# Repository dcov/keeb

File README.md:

# keeb

### controller
Contains the KiCad project files for the main micro controller.
Since this is a split keyboard, this controller is designed to be used in master and slave mode.

### sensor
Contains the KiCad project files for the mouse sensor board for the trackballs.

### stick
Contains the KiCad project files for the joystick boards.

### other components are WIP

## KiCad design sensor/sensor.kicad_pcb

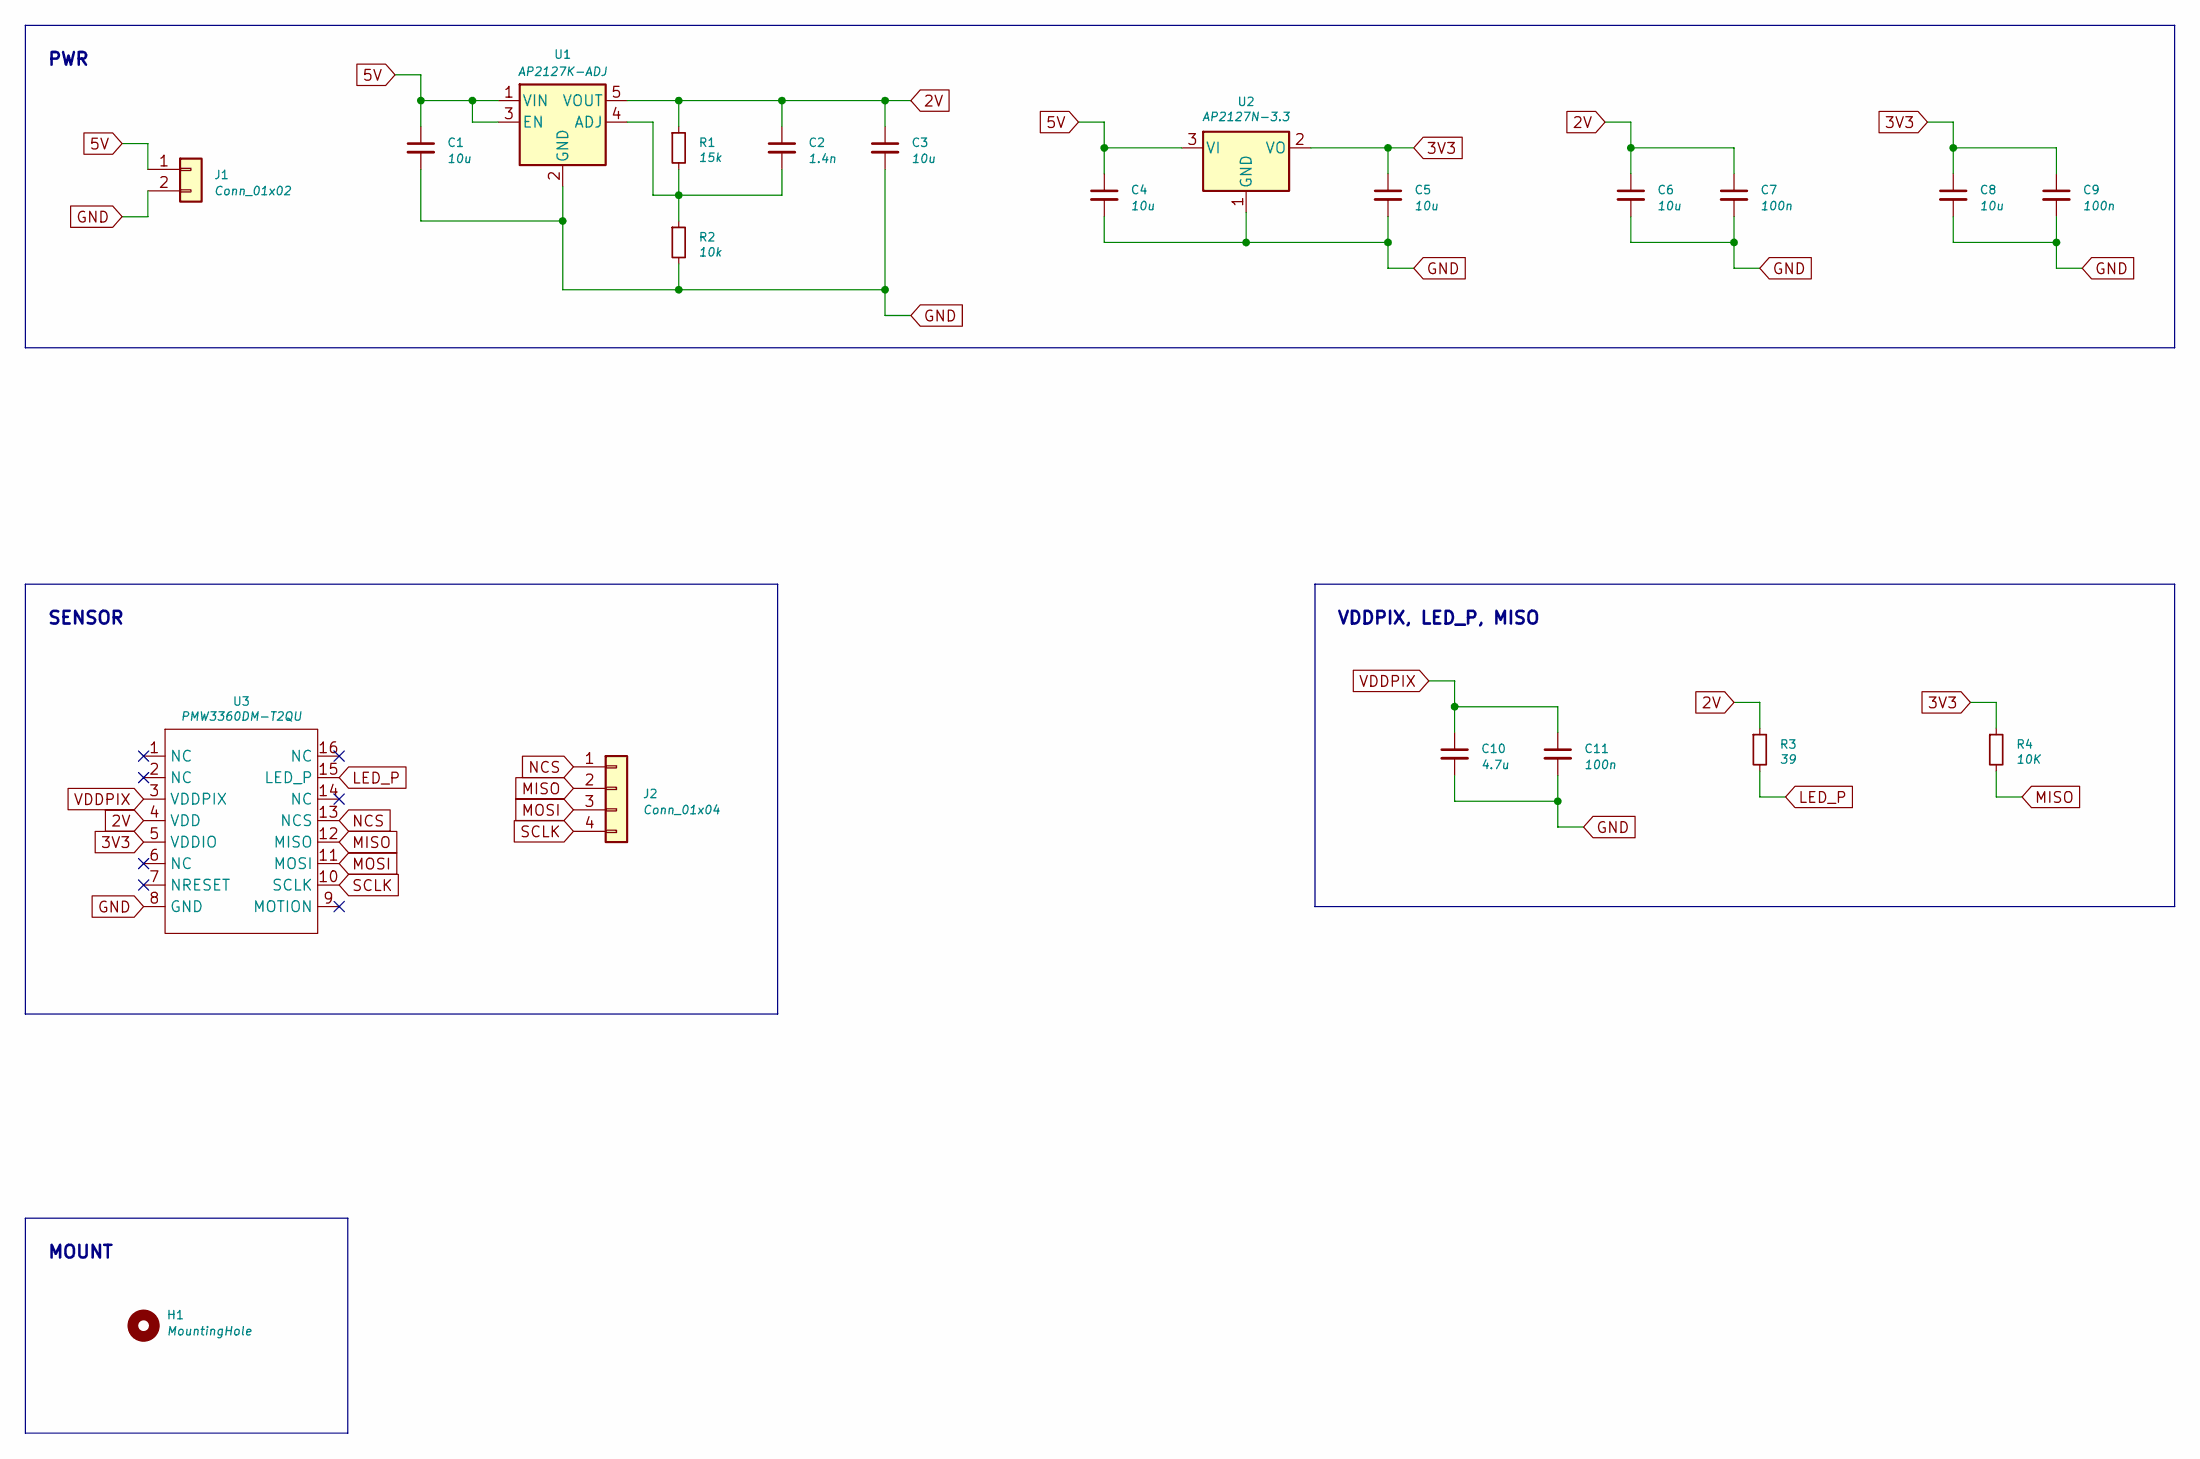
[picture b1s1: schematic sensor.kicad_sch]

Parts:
C1, C3, C4, C5, C6, C8: 10u; C_0603_1608Metric
C2: 1.4n; C_0603_1608Metric
C7, C9, C11: 100n; C_0603_1608Metric
C10: 4.7u; C_0603_1608Metric
H1: MountingHole; MountingHole_2.2mm_M2_Pad
J1: Conn_01x02; MOLEX_533750210-Mini-Lock-2Pin-Through-Hole
J2: Conn_01x04; Molex_PicoBlade_53047-0410_1x04_P1.25mm_Vertical
R1: 15k; R_0603_1608Metric
R2: 10k; R_0603_1608Metric
R3: 39; R_0603_1608Metric
R4: 10K; R_0603_1608Metric
U1: AP2127K-ADJ; SOT-23-5
U2: AP2127N-3.3; SOT-23
U3: PMW3360DM-T2QU

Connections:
2V: C2.1, C3.1, C6.1, C7.1, R1.1, R3.1, U1.5 (VOUT), U3.4 (VDD)
3V3: C5.1, C8.1, C9.1, R4.1, U2.2 (VO), U3.5 (VDDIO)
5V: C1.1, C4.1, J1.1, U1.1 (VIN), U1.3 (EN), U2.3 (VI); also elsewhere on the board
GND: C1.2, C3.2, C4.2, C5.2, C6.2, C7.2, C8.2, C9.2, C10.2, C11.2, J1.2, R2.2, U1.2 (GND), U2.1 (GND), U3.8 (GND); also elsewhere on the board
LED_P: R3.2, U3.15 (LED_P)
MISO: J2.2, R4.2, U3.12 (MISO)
MOSI: J2.3, U3.11 (MOSI)
NCS: J2.1, U3.13 (NCS)
unnamed: C2.2, R1.2, R2.1, U1.4 (ADJ)
SCLK: J2.4, U3.10 (SCLK)
VDDPIX: C10.1, C11.1, U3.3 (VDDPIX)

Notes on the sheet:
PWR
SENSOR
VDDPIX, LED_P, MISO
MOUNT

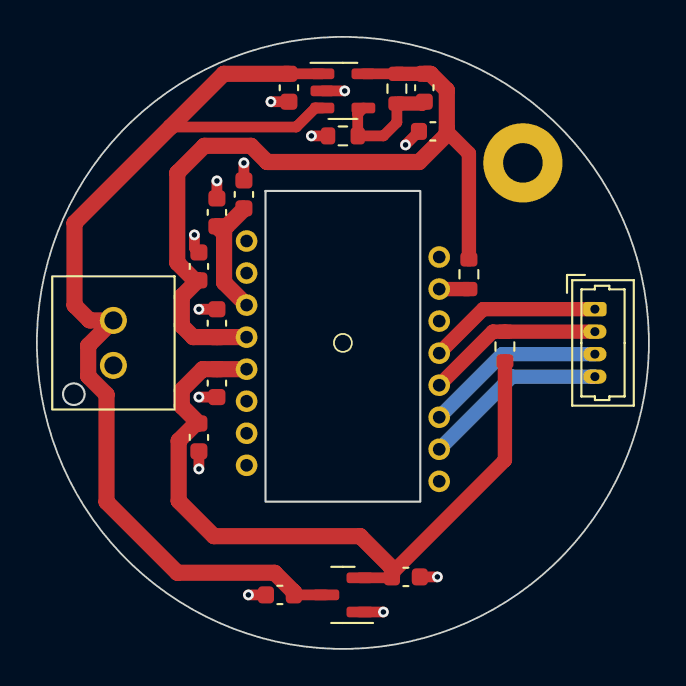
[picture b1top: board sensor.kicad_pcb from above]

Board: 2 copper layers, 34.0 x 34.0 mm, 21 parts (0 on the bottom side), 11 nets.

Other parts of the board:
Ce: 10u; C_0603_1608Metric

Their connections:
5V: Ce.1; also elsewhere on the board
GND: Ce.2; also elsewhere on the board

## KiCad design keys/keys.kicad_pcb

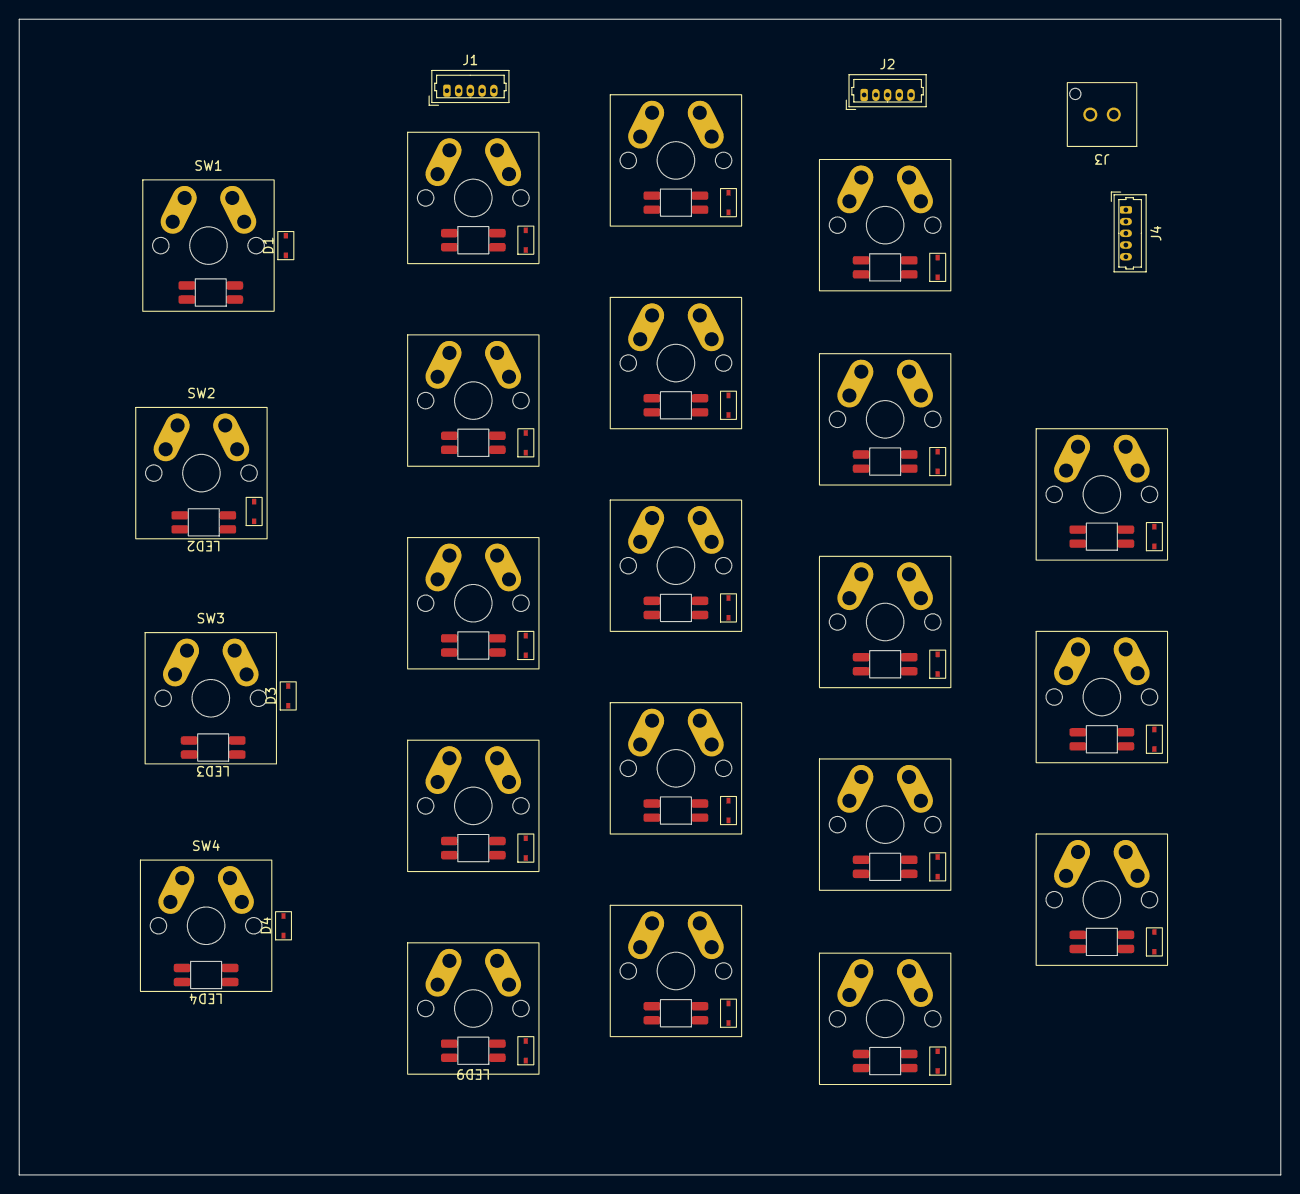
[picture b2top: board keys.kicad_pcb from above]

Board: 2 copper layers, 134.4 x 123.2 mm, 70 parts (0 on the bottom side), 56 nets, no tracks yet.

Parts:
D1, D2, D3, D4, D5, D6, D7, D8, D9, D10, D11, D12, D13, D14, D15, D16, D17, D18, D19, D20, D21, D22: D_Schottky; SMD_D-SOD-323-Reversible
J1, J2, J4: Conn_01x05; Molex_PicoBlade_53047-0510_1x05_P1.25mm_Vertical
J3: Conn_01x02; MOLEX_533750210-Mini-Lock-2Pin-Through-Hole
LED1, LED2, LED3, LED4, LED5, LED6, LED7, LED8, LED9, LED10, LED11, LED13, LED14, LED15, LED16, LED17, LED18, LED19, LED20, LED21, LED22: SK6812MINI-E; OPSCO_SK6812MINI-E
LEDe: SK6812MINI-E; OPSCO_SK6812MINI-E
SW1, SW2, SW3, SW4, SW5, SW6, SW7, SW8, SW9, SW10, SW11, SW12, SW13, SW14, SW15, SW16, SW17, SW18, SW19, SW20, SW21, SW22: SW_SPST; CHERRY_MX_SW-PCB-Reversible

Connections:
5V: J3.1, LED1.3 (VDD), LED2.3 (VDD), LED3.3 (VDD), LED4.3 (VDD), LED5.3 (VDD), LED6.3 (VDD), LED7.3 (VDD), LED8.3 (VDD), LED9.3 (VDD), LED10.3 (VDD), LED11.3 (VDD), LED13.3 (VDD), LED14.3 (VDD), LED15.3 (VDD), LED16.3 (VDD), LED17.3 (VDD), LED18.3 (VDD), LED19.3 (VDD), LED20.3 (VDD), LED21.3 (VDD), LED22.3 (VDD), LEDe.3 (VDD)
COL1: D1.1 (K), D2.1 (K), D3.1 (K), D4.1 (K), J1.1
COL1_DIN: J4.1, LED1.2 (DIN)
COL2: D5.1 (K), D6.1 (K), D7.1 (K), D8.1 (K), D9.1 (K), J1.2
COL2_DIN: J4.2, LED5.2 (DIN)
COL3: D10.1 (K), D11.1 (K), D12.1 (K), D13.1 (K), D14.1 (K), J1.3
COL3_DIN: J4.3, LED10.2 (DIN)
COL4: D15.1 (K), D16.1 (K), D17.1 (K), D18.1 (K), D19.1 (K), J1.4
COL4_DIN: J4.4, LED15.2 (DIN)
COL5: D20.1 (K), D21.1 (K), D22.1 (K), J1.5
COL5_DIN: J4.5, LED20.2 (DIN)
GND: J3.2, LED1.1 (GND), LED2.1 (GND), LED3.1 (GND), LED4.1 (GND), LED5.1 (GND), LED6.1 (GND), LED7.1 (GND), LED8.1 (GND), LED9.1 (GND), LED10.1 (GND), LED11.1 (GND), LED13.1 (GND), LED14.1 (GND), LED15.1 (GND), LED16.1 (GND), LED17.1 (GND), LED18.1 (GND), LED19.1 (GND), LED20.1 (GND), LED21.1 (GND), LED22.1 (GND), LEDe.1 (GND)
unnamed: D1.2 (A), SW1.2 (B)
unnamed: D2.2 (A), SW2.2 (B)
unnamed: D3.2 (A), SW3.2 (B)
unnamed: D4.2 (A), SW4.2 (B)
unnamed: D5.2 (A), SW5.2 (B)
unnamed: D6.2 (A), SW6.2 (B)
unnamed: D7.2 (A), SW7.2 (B)
unnamed: D8.2 (A), SW8.2 (B)
unnamed: D9.2 (A), SW9.2 (B)
unnamed: D10.2 (A), SW10.2 (B)
unnamed: D11.2 (A), SW11.2 (B)
unnamed: D12.2 (A), SW12.2 (B)
unnamed: D13.2 (A), SW13.2 (B)
unnamed: D14.2 (A), SW14.2 (B)
unnamed: D15.2 (A), SW15.2 (B)
unnamed: D16.2 (A), SW16.2 (B)
unnamed: D17.2 (A), SW17.2 (B)
unnamed: D18.2 (A), SW18.2 (B)
unnamed: D19.2 (A), SW19.2 (B)
unnamed: D20.2 (A), SW20.2 (B)
unnamed: D21.2 (A), SW21.2 (B)
unnamed: D22.2 (A), SW22.2 (B)
unnamed: LED1.4 (DOUT), LED2.2 (DIN)
unnamed: LED2.4 (DOUT), LED3.2 (DIN)
unnamed: LED3.4 (DOUT), LED4.2 (DIN)
unnamed: LED5.4 (DOUT), LED6.2 (DIN)
unnamed: LED6.4 (DOUT), LED7.2 (DIN)
unnamed: LED7.4 (DOUT), LED8.2 (DIN)
unnamed: LED8.4 (DOUT), LED9.2 (DIN)
unnamed: LED10.4 (DOUT), LED11.2 (DIN)
unnamed: LED11.4 (DOUT), LEDe.2 (DIN)
unnamed: LED13.2 (DIN), LEDe.4 (DOUT)
unnamed: LED13.4 (DOUT), LED14.2 (DIN)
unnamed: LED15.4 (DOUT), LED16.2 (DIN)
unnamed: LED16.4 (DOUT), LED17.2 (DIN)
unnamed: LED17.4 (DOUT), LED18.2 (DIN)
unnamed: LED18.4 (DOUT), LED19.2 (DIN)
unnamed: LED20.4 (DOUT), LED21.2 (DIN)
unnamed: LED21.4 (DOUT), LED22.2 (DIN)
ROW1: J2.1, SW1.1 (A), SW5.1 (A), SW10.1 (A), SW15.1 (A), SW20.1 (A)
ROW2: J2.2, SW2.1 (A), SW6.1 (A), SW11.1 (A), SW16.1 (A), SW21.1 (A)
ROW3: J2.3, SW3.1 (A), SW7.1 (A), SW12.1 (A), SW17.1 (A), SW22.1 (A)
ROW4: J2.4, SW4.1 (A), SW8.1 (A), SW13.1 (A), SW18.1 (A)
ROW5: J2.5, SW9.1 (A), SW14.1 (A), SW19.1 (A)

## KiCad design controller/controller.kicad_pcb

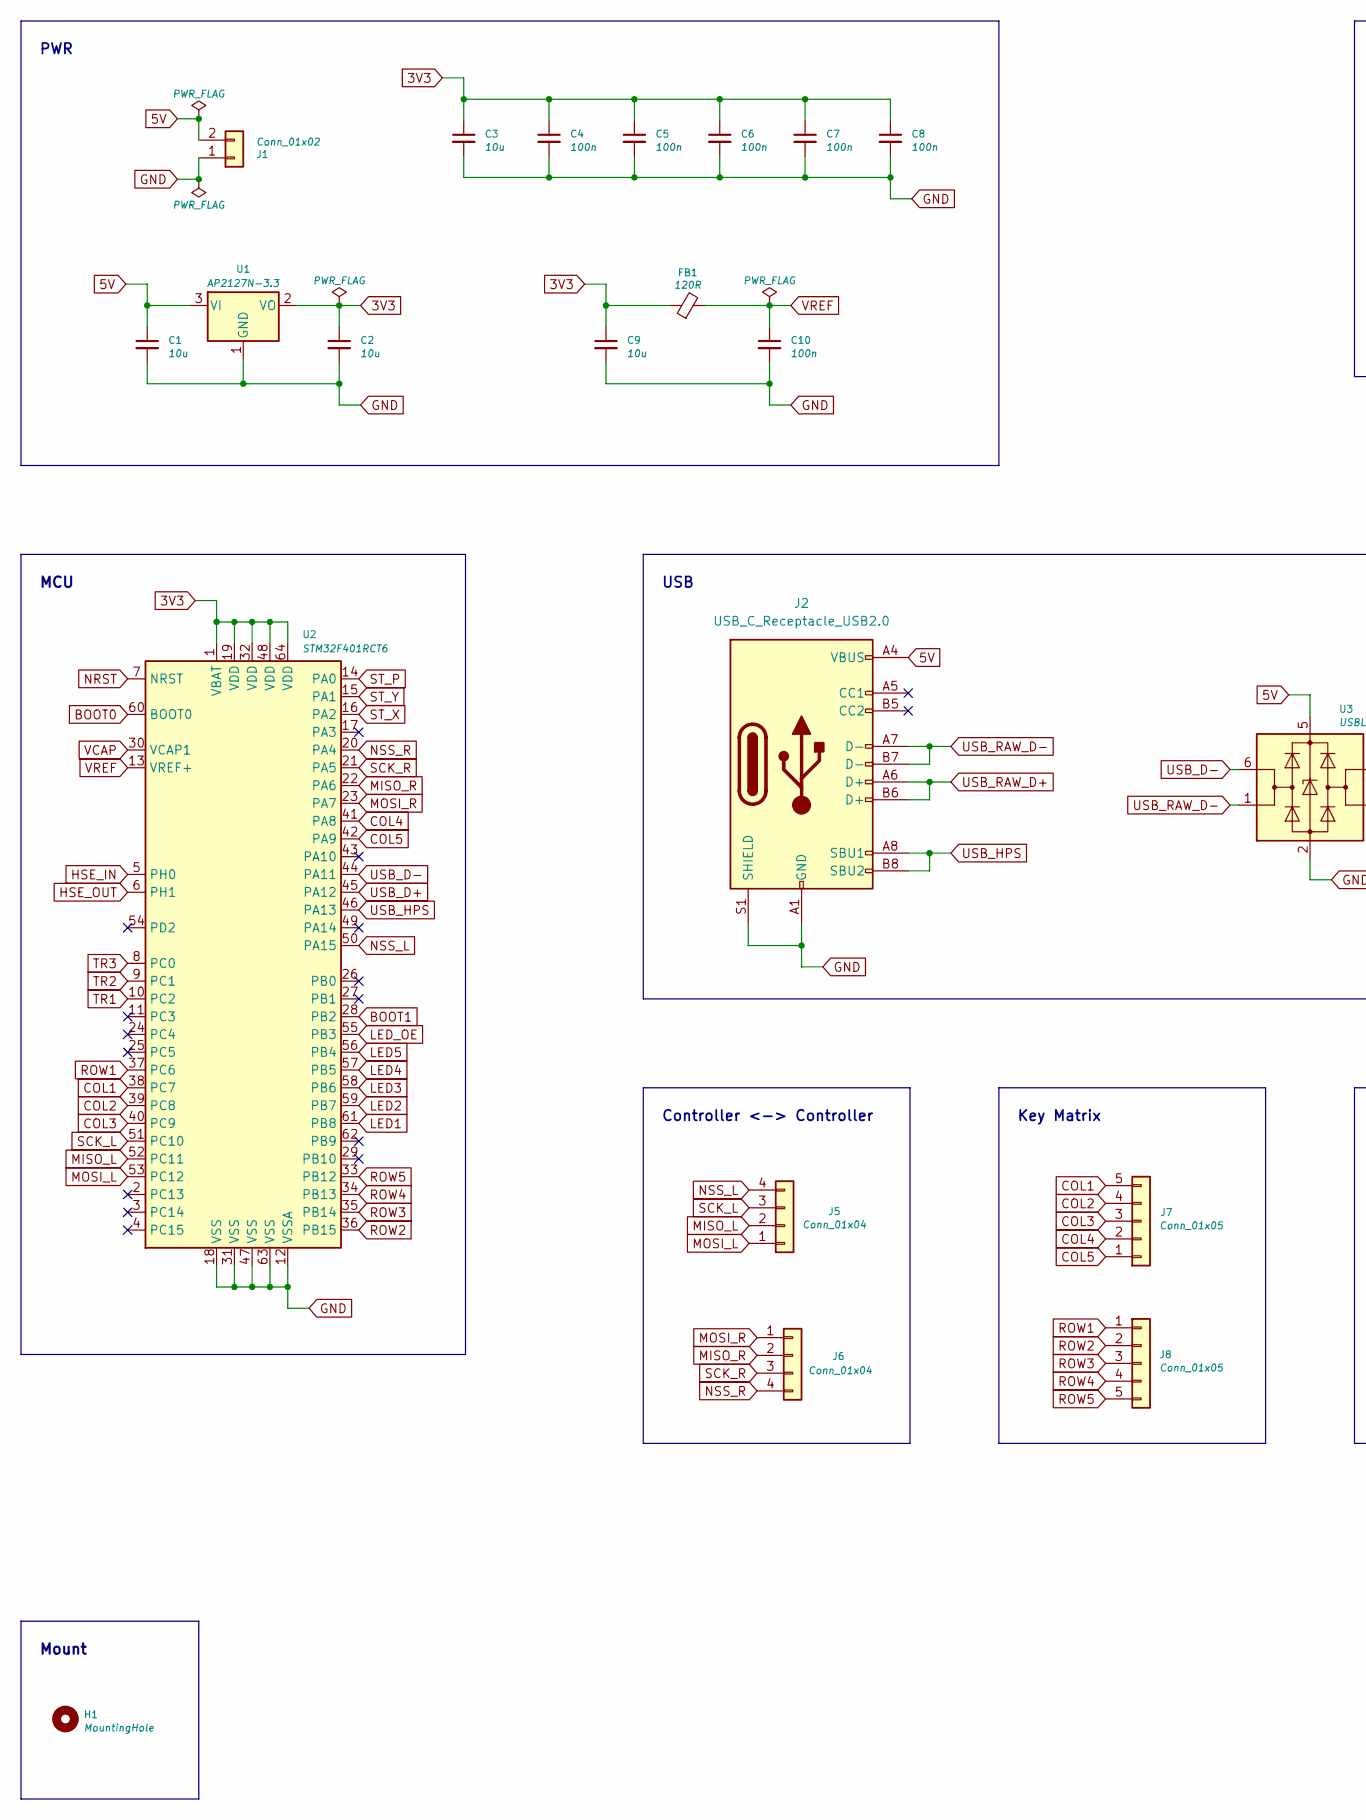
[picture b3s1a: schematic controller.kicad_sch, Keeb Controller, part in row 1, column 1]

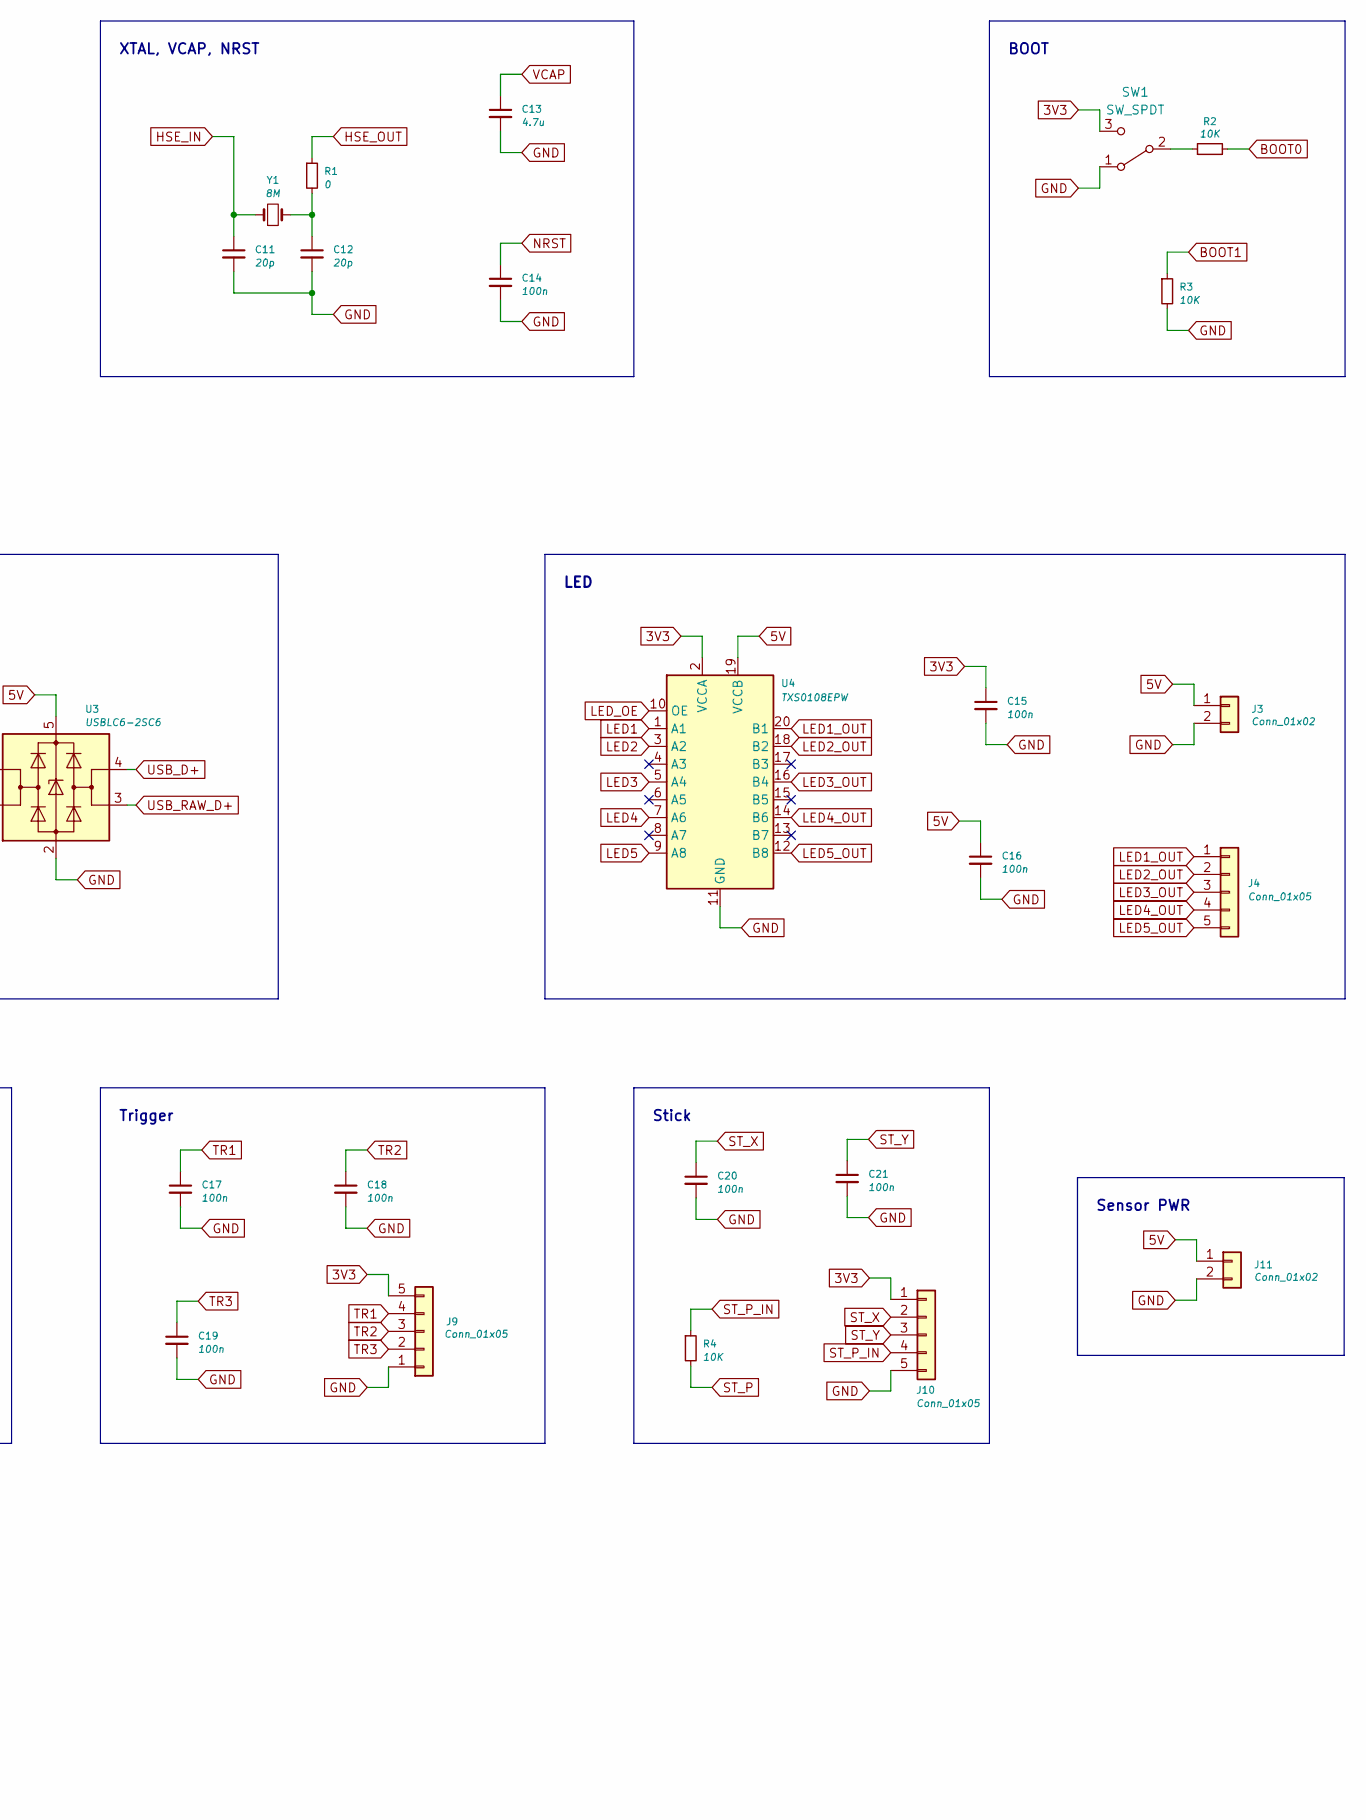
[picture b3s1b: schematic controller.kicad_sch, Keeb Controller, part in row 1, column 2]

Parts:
C1, C2, C3, C9: 10u; C_0603_1608Metric
C4, C5, C6, C7, C8, C10, C14, C15, C16, C17, C18, C19, C20, C21: 100n; C_0603_1608Metric
C11, C12: 20p; C_0603_1608Metric
C13: 4.7u; C_0603_1608Metric
FB1: 120R; L_0603_1608Metric
H1: MountingHole; MountingHole_2.2mm_M2_Pad
J1, J3, J11: Conn_01x02; MOLEX_533750210-Mini-Lock-2Pin-Through-Hole
J2: USB_C_Receptacle_USB2.0; USB_C_Receptacle_HRO_TYPE-C-31-M-12
J4, J7, J8, J9, J10: Conn_01x05; Molex_PicoBlade_53047-0510_1x05_P1.25mm_Vertical
J5, J6: Conn_01x04; Molex_PicoBlade_53047-0410_1x04_P1.25mm_Vertical
R1: 0; R_0603_1608Metric
R2, R3, R4: 10K; R_0603_1608Metric
SW1: SW_SPDT; ALPS_SSSS912000
U1: AP2127N-3.3; SOT-23
U2: STM32F401RCT6; LQFP-64_10x10mm_P0.5mm
U3: USBLC6-2SC6; SOT-23-6
U4: TXS0108EPW; TSSOP-20_4.4x6.5mm_P0.65mm
Y1: 8M; Crystal_SMD_5032-2Pin_5.0x3.2mm

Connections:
3V3: C2.1, C3.1, C4.1, C5.1, C6.1, C7.1, C8.1, C9.1, C15.1, FB1.1, J9.5, J10.1, SW1.3 (C), U1.2 (VO), U2.1 (VBAT), U2.19 (VDD), U2.32 (VDD), U2.48 (VDD), U2.64 (VDD), U4.2 (VCCA)
5V: C1.1, C16.1, J1.2, J2.A4 (VBUS), J2.A9 (VBUS), J2.B4 (VBUS), J2.B9 (VBUS), J3.1, J11.1, U1.3 (VI), U3.5 (VBUS), U4.19 (VCCB)
BOOT0: R2.2, U2.60 (BOOT0)
BOOT1: R3.1, U2.28 (PB2)
COL1: J7.5, U2.38 (PC7)
COL2: J7.4, U2.39 (PC8)
COL3: J7.3, U2.40 (PC9)
COL4: J7.2, U2.41 (PA8)
COL5: J7.1, U2.42 (PA9)
GND: C1.2, C2.2, C3.2, C4.2, C5.2, C6.2, C7.2, C8.2, C9.2, C10.2, C11.2, C12.2, C13.2, C14.2, C15.2, C16.2, C17.2, C18.2, C19.2, C20.2, C21.2, J1.1, J2.A1 (GND), J2.A12 (GND), J2.B1 (GND), J2.B12 (GND), J2.S1 (SHIELD), J3.2, J9.1, J10.5, J11.2, R3.2, SW1.1 (A), U1.1 (GND), U2.12 (VSSA), U2.18 (VSS), U2.31 (VSS), U2.47 (VSS), U2.63 (VSS), U3.2 (GND), U4.11 (GND)
HSE_IN: C11.1, U2.5 (PH0), Y1.1
HSE_OUT: R1.1, U2.6 (PH1)
LED1: U2.61 (PB8), U4.1 (A1)
LED1_OUT: J4.1, U4.20 (B1)
LED2: U2.59 (PB7), U4.3 (A2)
LED2_OUT: J4.2, U4.18 (B2)
LED3: U2.58 (PB6), U4.5 (A4)
LED3_OUT: J4.3, U4.16 (B4)
LED4: U2.57 (PB5), U4.7 (A6)
LED4_OUT: J4.4, U4.14 (B6)
LED5: U2.56 (PB4), U4.9 (A8)
LED5_OUT: J4.5, U4.12 (B8)
LED_OE: U2.55 (PB3), U4.10 (OE)
MISO_L: J5.2, U2.52 (PC11)
MISO_R: J6.2, U2.22 (PA6)
MOSI_L: J5.1, U2.53 (PC12)
MOSI_R: J6.1, U2.23 (PA7)
NRST: C14.1, U2.7 (NRST)
NSS_L: J5.4, U2.50 (PA15)
NSS_R: J6.4, U2.20 (PA4)
unnamed: C12.1, R1.2, Y1.2
unnamed: R2.1, SW1.2 (B)
ROW1: J8.1, U2.37 (PC6)
ROW2: J8.2, U2.36 (PB15)
ROW3: J8.3, U2.35 (PB14)
ROW4: J8.4, U2.34 (PB13)
ROW5: J8.5, U2.33 (PB12)
SCK_L: J5.3, U2.51 (PC10)
SCK_R: J6.3, U2.21 (PA5)
ST_P: R4.2, U2.14 (PA0)
ST_P_IN: J10.4, R4.1
ST_X: C20.1, J10.2, U2.16 (PA2)
ST_Y: C21.1, J10.3, U2.15 (PA1)
TR1: C17.1, J9.4, U2.10 (PC2)
TR2: C18.1, J9.3, U2.9 (PC1)
TR3: C19.1, J9.2, U2.8 (PC0)
USB_D+: U2.45 (PA12), U3.4 (I/O2)
USB_D-: U2.44 (PA11), U3.6 (I/O1)
USB_HPS: J2.A8 (SBU1), J2.B8 (SBU2), U2.46 (PA13)
USB_RAW_D+: J2.A6 (D+), J2.B6 (D+), U3.3 (I/O2)
USB_RAW_D-: J2.A7 (D-), J2.B7 (D-), U3.1 (I/O1)
VCAP: C13.1, U2.30 (VCAP1)
VREF: C10.1, FB1.2, U2.13 (VREF+)

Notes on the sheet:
PWR
BOOT
LED
Mount
USB
XTAL, VCAP, NRST
Trigger
Sensor PWR
Stick
Controller <-> Controller
MCU
Key Matrix

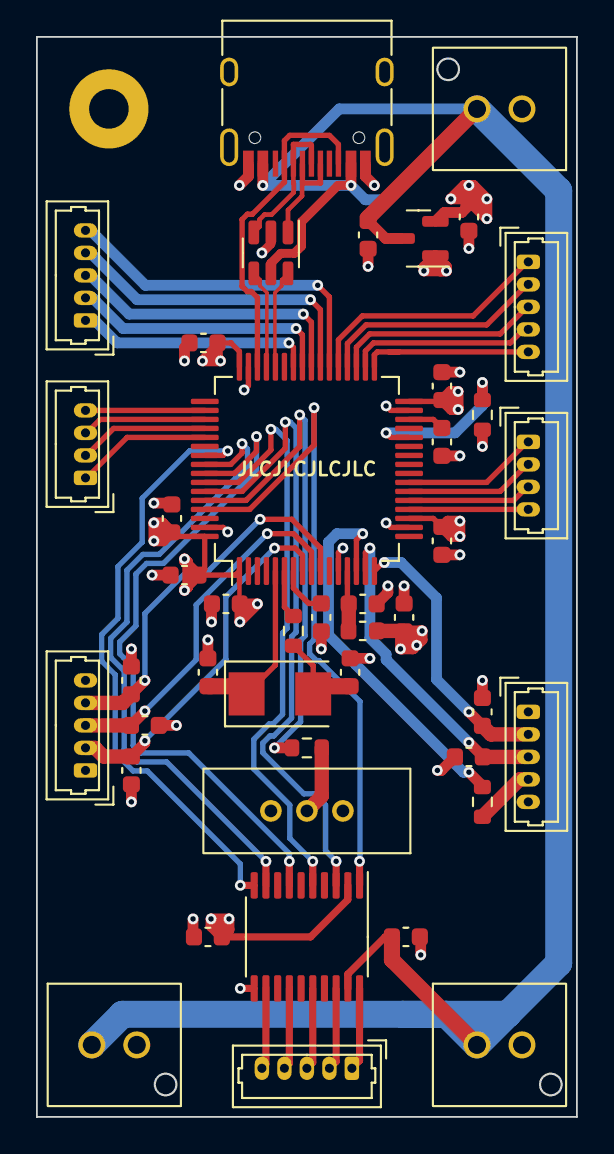
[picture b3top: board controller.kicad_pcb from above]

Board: 4 copper layers, 30.0 x 60.0 mm, 44 parts (0 on the bottom side), 53 nets.

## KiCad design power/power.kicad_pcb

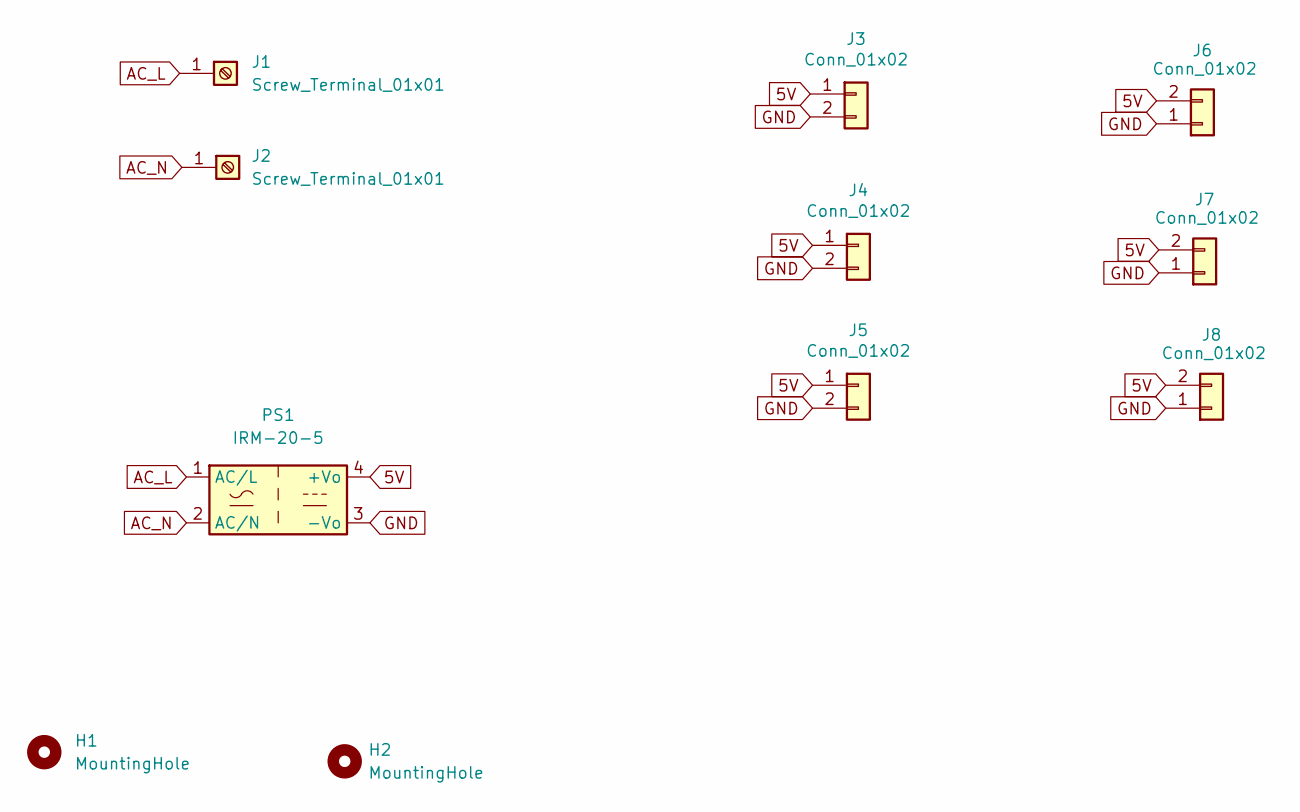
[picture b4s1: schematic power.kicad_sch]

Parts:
H1, H2: MountingHole; MountingHole_2.2mm_M2_Pad
J1, J2: Screw_Terminal_01x01; DORABO_DB136HA-10.16-1P
J3, J4, J5, J6, J7, J8: Conn_01x02; MOLEX_533750210-Mini-Lock-2Pin-Through-Hole
PS1: IRM-20-5; Converter_ACDC_MeanWell_IRM-20-xx_THT

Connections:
5V: J3.1, J4.1, J5.1, J6.2, J7.2, J8.2, PS1.4 (+Vo)
AC_L: J1.1, PS1.1 (AC/L)
AC_N: J2.1, PS1.2 (AC/N)
GND: J3.2, J4.2, J5.2, J6.1, J7.1, J8.1, PS1.3 (-Vo)

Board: 2 copper layers, 11 parts (0 on the bottom side), 4 nets, no tracks yet.

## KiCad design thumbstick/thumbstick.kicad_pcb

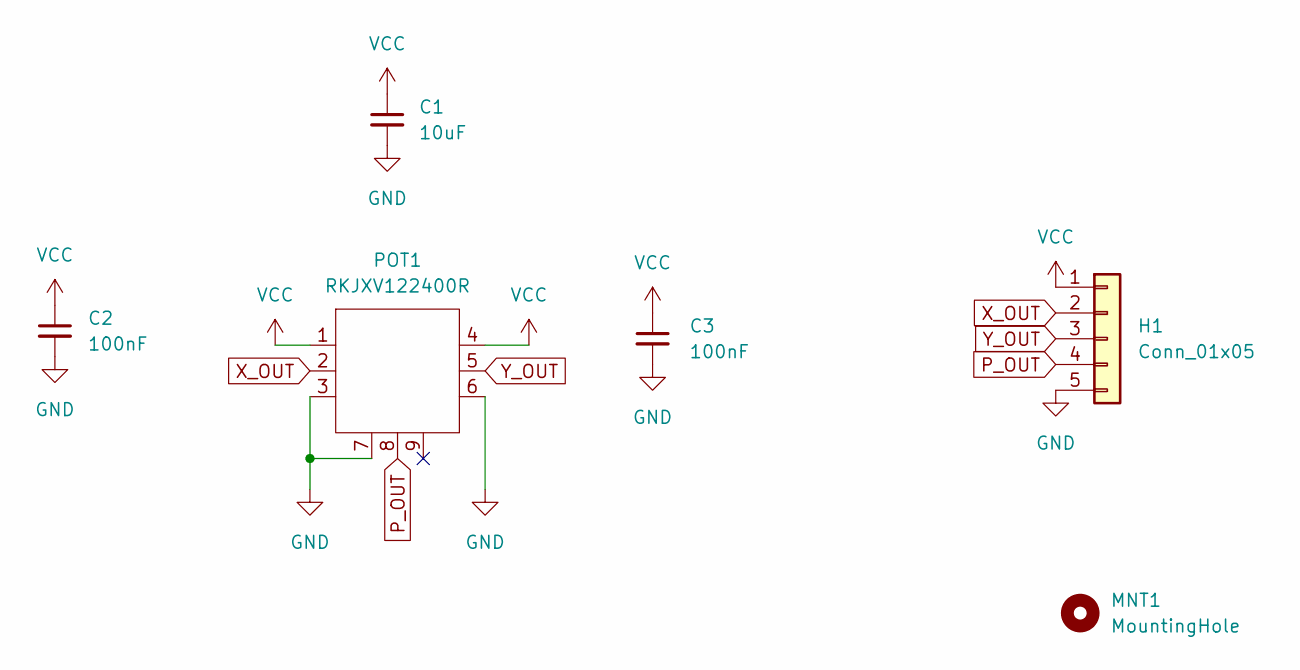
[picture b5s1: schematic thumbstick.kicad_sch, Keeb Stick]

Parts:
C1: 10uF; C_0603_1608Metric
C2, C3: 100nF; C_0603_1608Metric
H1: Conn_01x05; Molex_PicoBlade_53047-0510_1x05_P1.25mm_Vertical
MNT1: MountingHole; MountingHole_2.2mm_M2_Pad
POT1: RKJXV122400R

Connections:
GND: C1.2, C2.2, C3.2, H1.5, POT1.3, POT1.6, POT1.7
P_OUT: H1.4, POT1.8
VCC: C1.1, C2.1, C3.1, H1.1, POT1.1, POT1.4
X_OUT: H1.2, POT1.2
Y_OUT: H1.3, POT1.5

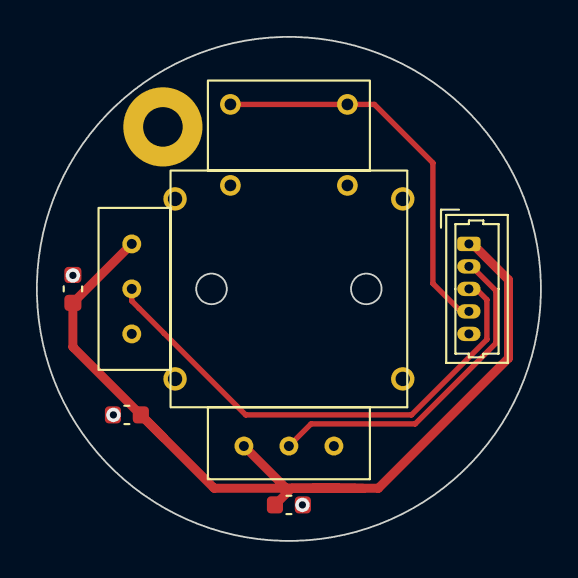
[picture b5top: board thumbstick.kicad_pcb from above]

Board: 2 copper layers, 28.0 x 28.0 mm, 6 parts (0 on the bottom side), 5 nets.

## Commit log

2022-11-02 switching os
2022-11-13 Controller v1
2022-11-14 Sensor v1
2022-11-14 Thubmstick v1
2022-11-19 start work on host mcu
2022-11-21 assigned host pins
2022-11-24 host v1
2022-11-25 start power board
2022-11-30 power v1, updated host to v2
2022-12-02 update controller and host boards
2022-12-02 move thumbstick/ to stick/, update keys layout, delete obsolete trackball project
2022-12-06 update sensor and stick, add trigger project
2024-02-12 minimal README
